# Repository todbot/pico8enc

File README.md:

# pico8enc -- 8 rotary encoders on a Raspberry Pi Pico

Turns out you can hook up 8 rotary encoders w/ switches to
Raspberry Pi Pico with no extra hardware. Pretty cool!

With CircuitPython, it becomes pretty easy to actually read these encoders
since all hard, timing-critical work is done inside the C-based `rotaryio`
library that comes standard with CircuitPython.

One "twist" to look out for (haha): the two rotary encoder pins must be hooked up
to adjacent pins on the Pico, because of how `rotaryio` uses the Pico's
PIO module to handle reading the encoder pulses.

The core of the code looks like this:
```py
encoder_pins = ( (board.GP12, board.GP13, board.GP16),  # pin A, pin B, pin for switch
                 (board.GP10, board.GP11, board.GP17),
                 (board.GP8, board.GP9, board.GP18),
                 (board.GP6, board.GP7, board.GP19),
                 # ...
                 )
encoders = []
encoder_buttons = []
for pins in encoder_pins:
    pin_A, pin_B, pin_switch = pins
    encoder = rotaryio.IncrementalEncoder( pin_A, pin_B )
    button = DigitalInOut(pin_switch)
    button.pull = Pull.UP
    encoders.append(encoder)
    encoder_buttons.append(button)

while True:
    for i in range(len(encoders)):
      position = encoders[i].position
      button_press = encoder_buttons[i].value

```

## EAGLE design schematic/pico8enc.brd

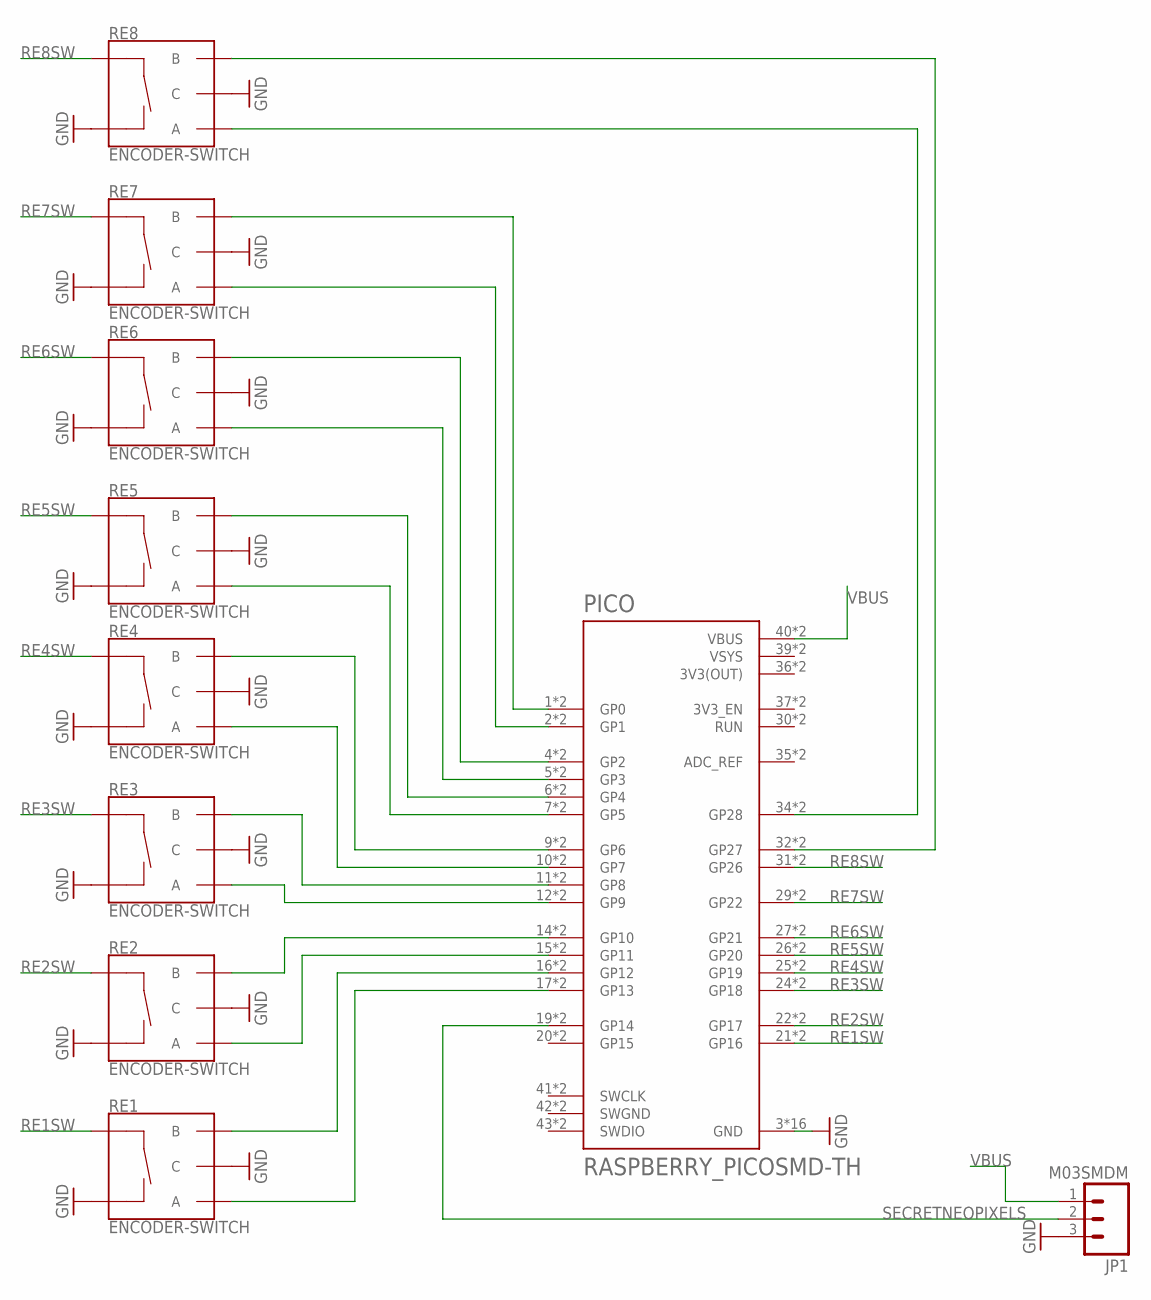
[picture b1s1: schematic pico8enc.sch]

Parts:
JP1: M03SMDM; 1X03-SMD-MINIMAL
PICO: RASPBERRY_PICOSMD-TH; PICO-PKG
RE1, RE2, RE3, RE4, RE5, RE6, RE7, RE8: ENCODER-SWITCH; ROTARY_ENC_PLAIN

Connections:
3V3(OUT): PICO.36 (3V3(OUT)), PICO.P$36 (3V3(OUT))
GND: JP1.3, PICO.3 (GND), PICO.8 (GND), PICO.13 (GND), PICO.18 (GND), PICO.23 (GND), PICO.28 (GND), PICO.33 (GND), PICO.38 (GND), PICO.P$3 (GND), PICO.P$8 (GND), PICO.P$13 (GND), PICO.P$18 (GND), PICO.P$23 (GND), PICO.P$28 (GND), PICO.P$33 (GND), PICO.P$38 (GND), RE1.C, RE1.SW-, RE2.C, RE2.SW-, RE3.C, RE3.SW-, RE4.C, RE4.SW-, RE5.C, RE5.SW-, RE6.C, RE6.SW-, RE7.C, RE7.SW-, RE8.C, RE8.SW-
unnamed: PICO.17 (GP13), PICO.P$17 (GP13), RE1.A
unnamed: PICO.16 (GP12), PICO.P$16 (GP12), RE1.B
unnamed: PICO.15 (GP11), PICO.P$15 (GP11), RE2.A
unnamed: PICO.14 (GP10), PICO.P$14 (GP10), RE2.B
unnamed: PICO.12 (GP9), PICO.P$12 (GP9), RE3.A
unnamed: PICO.11 (GP8), PICO.P$11 (GP8), RE3.B
unnamed: PICO.10 (GP7), PICO.P$10 (GP7), RE4.A
unnamed: PICO.9 (GP6), PICO.P$9 (GP6), RE4.B
unnamed: PICO.7 (GP5), PICO.P$7 (GP5), RE5.A
unnamed: PICO.6 (GP4), PICO.P$6 (GP4), RE5.B
unnamed: PICO.5 (GP3), PICO.P$5 (GP3), RE6.A
unnamed: PICO.4 (GP2), PICO.P$4 (GP2), RE6.B
unnamed: PICO.2 (GP1), PICO.P$2 (GP1), RE7.A
unnamed: PICO.1 (GP0), PICO.P$1 (GP0), RE7.B
unnamed: PICO.34 (GP28), PICO.P$34 (GP28), RE8.A
unnamed: PICO.32 (GP27), PICO.P$32 (GP27), RE8.B
RE1SW: PICO.21 (GP16), PICO.P$21 (GP16), RE1.SW+
RE2SW: PICO.22 (GP17), PICO.P$22 (GP17), RE2.SW+
RE3SW: PICO.24 (GP18), PICO.P$24 (GP18), RE3.SW+
RE4SW: PICO.25 (GP19), PICO.P$25 (GP19), RE4.SW+
RE5SW: PICO.26 (GP20), PICO.P$26 (GP20), RE5.SW+
RE6SW: PICO.27 (GP21), PICO.P$27 (GP21), RE6.SW+
RE7SW: PICO.29 (GP22), PICO.P$29 (GP22), RE7.SW+
RE8SW: PICO.31 (GP26), PICO.P$31 (GP26), RE8.SW+
SECRETNEOPIXELS: JP1.2, PICO.19 (GP14), PICO.P$19 (GP14)
SWGND: PICO.42 (SWGND), PICO.P$42 (SWGND)
VBUS: JP1.1, PICO.40 (VBUS), PICO.P$40 (VBUS)
VSYS: PICO.39 (VSYS), PICO.P$39 (VSYS)

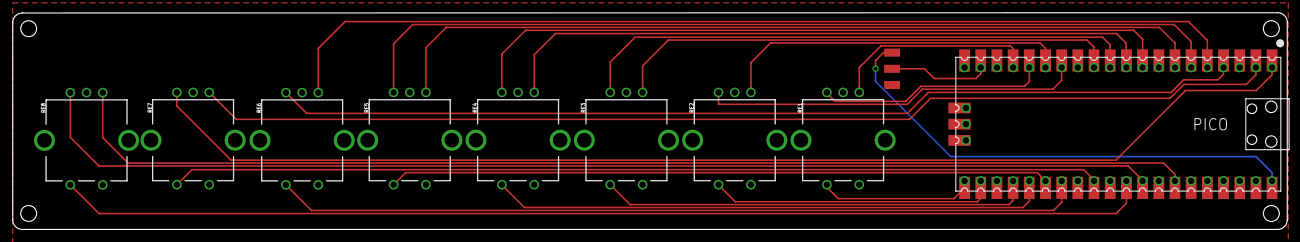
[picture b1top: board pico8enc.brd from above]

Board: 2 copper layers, 200.0 x 34.0 mm, 10 parts (0 on the bottom side), 30 nets.

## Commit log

2021-04-06 some ideas
2021-04-06 imgs
2021-04-13 update and made public since it made the CircuitPython newsletter
2021-04-13 bigger images
2021-04-13 some description
2021-04-13 small typo
2021-04-13 pin clarification
2021-04-15 pcb cleanup
2021-04-16 idea for front silk
2021-04-30 pcb syncup
2021-04-30 first cut at MIDI controller UI. looks like maybe cannot do 8 encoders and neopixel? PIO limit?
2021-04-30 code cleanup
2021-05-07 enable usb midi out
2021-05-07 added dualencoder pio hack version
2021-05-07 remove test comments
2021-05-07 make dualencoder version the "real" version
2021-05-07 added color to config show
2021-05-07 a little more docs in dualencoder
2021-05-07 small cleanup
2021-05-07 added idle knob color display
2021-05-07 added some install notes

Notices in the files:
parts and their libraries:
SparkFun-Switches: Licensing: Creative Commons ShareAlike 4.0 International - https://creativecommons.org/licenses/by-sa/4.0
